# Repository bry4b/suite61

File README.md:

# suite61
 split ergo with numrow, arrows, and a stick

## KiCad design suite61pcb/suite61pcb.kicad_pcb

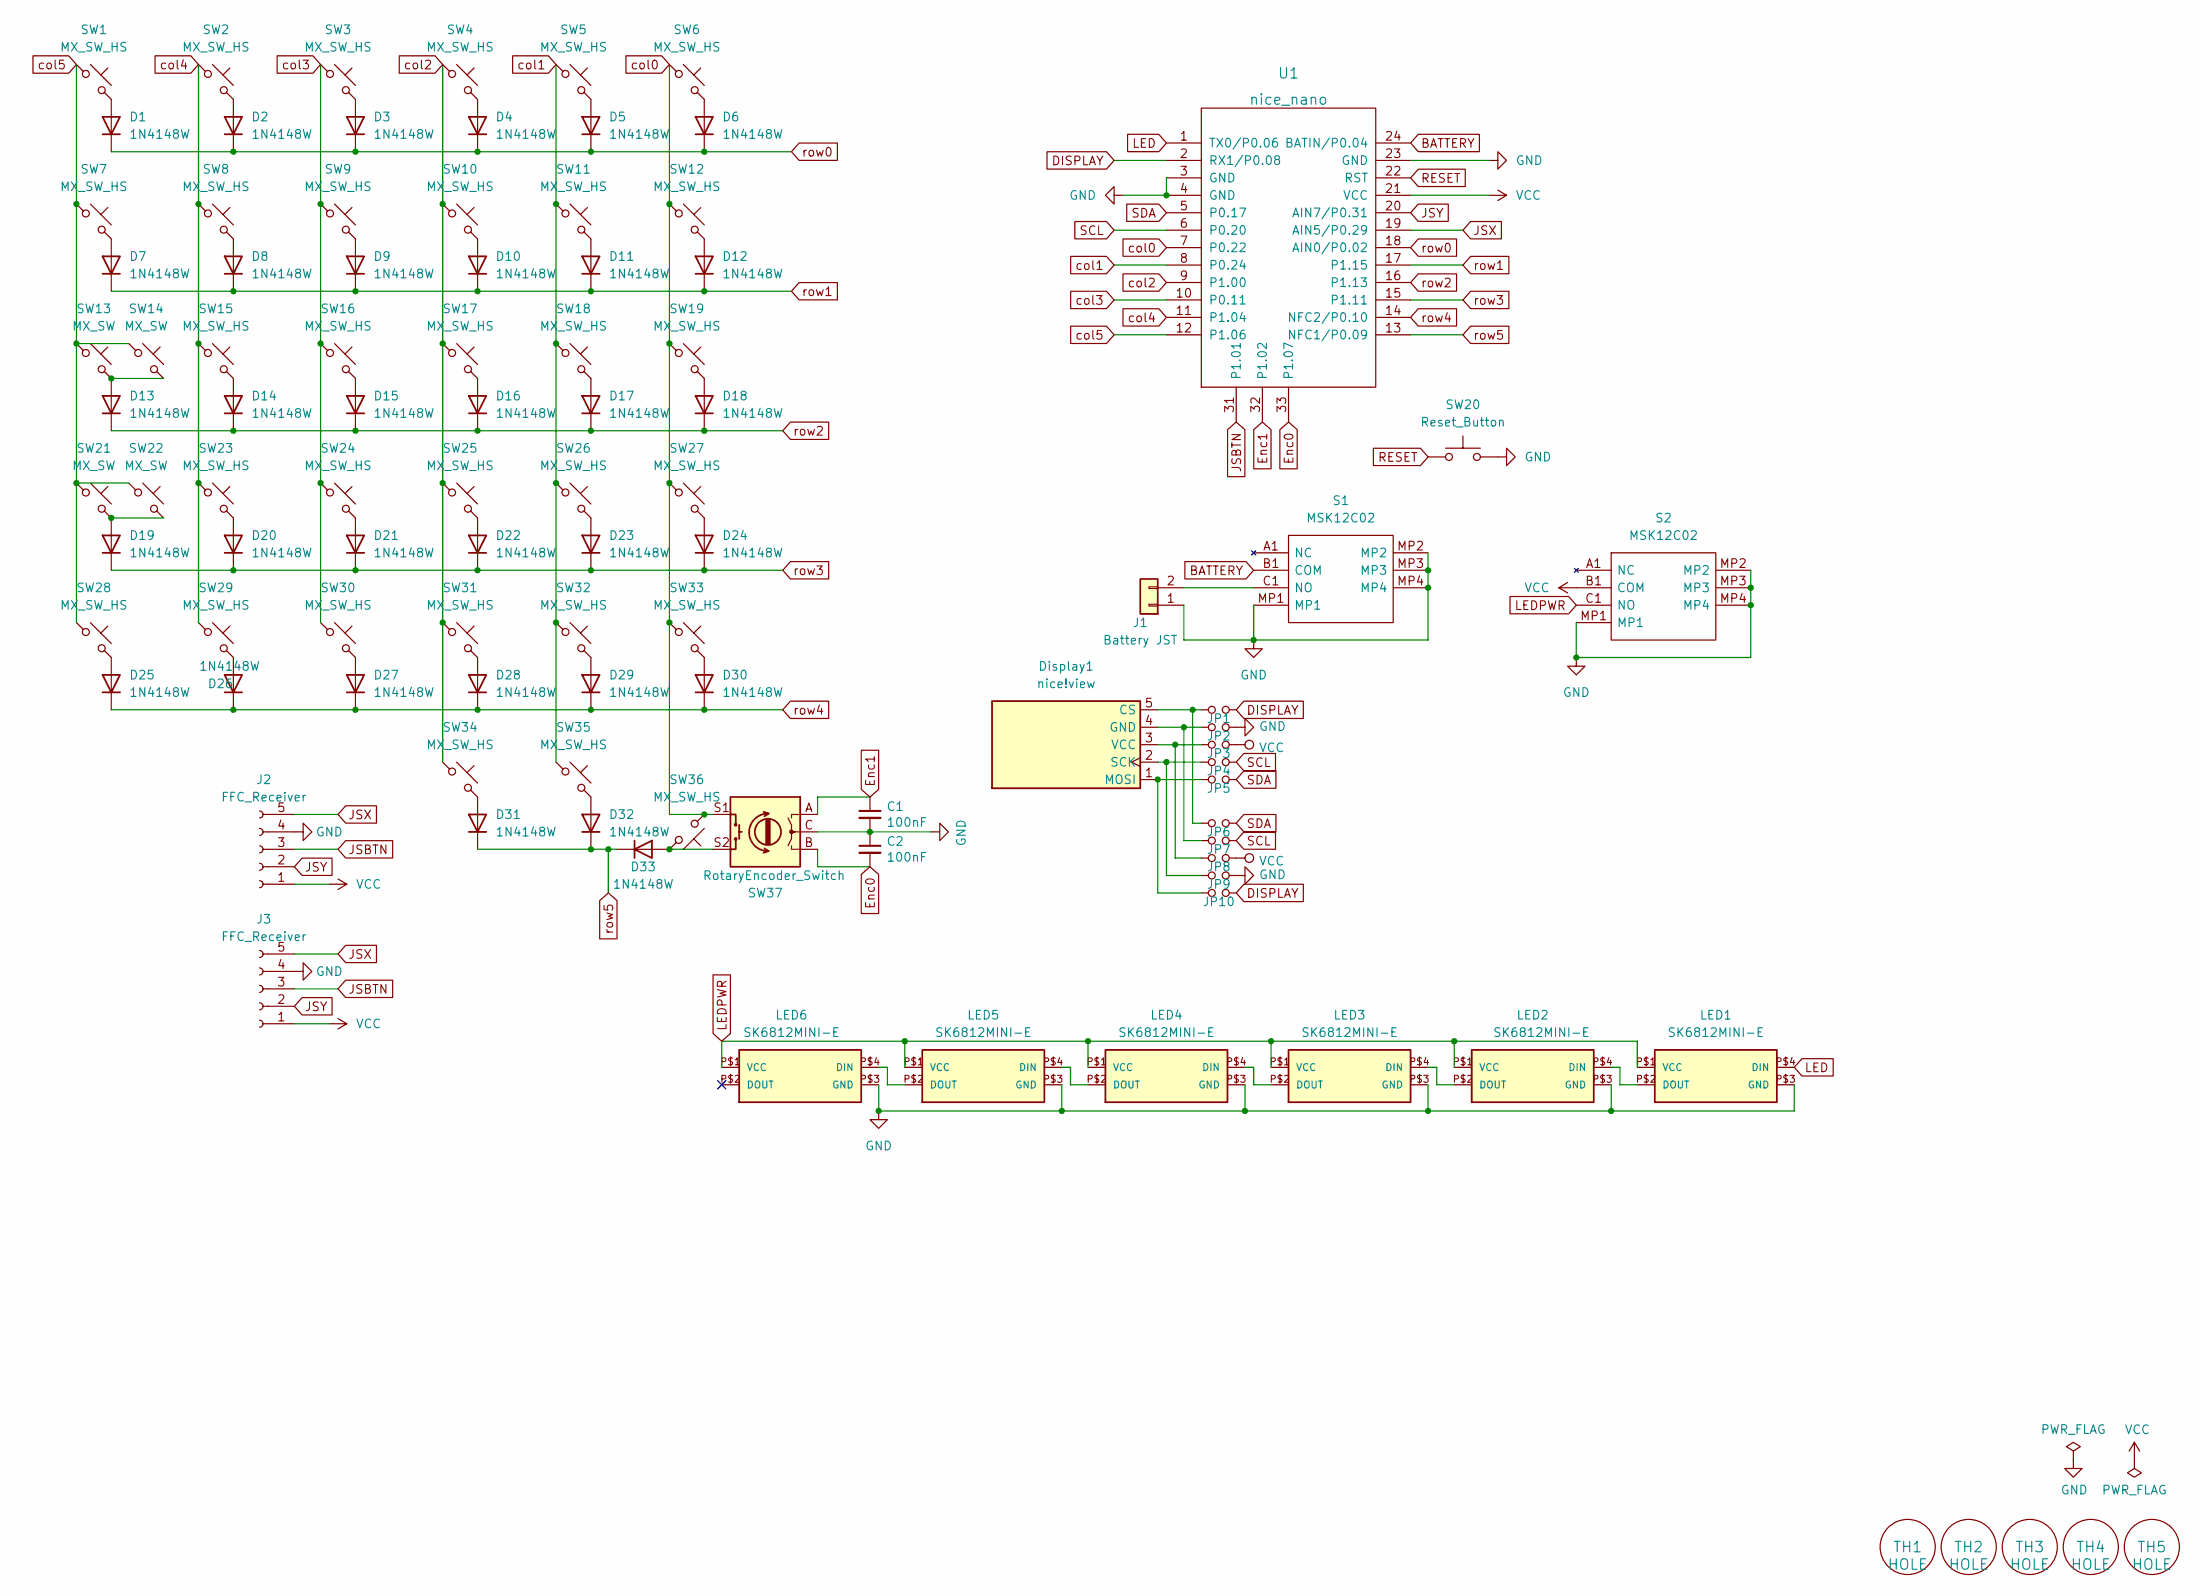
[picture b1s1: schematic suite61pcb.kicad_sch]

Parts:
C1, C2: 100nF; C_0805_2012Metric
D1, D2, D3, D4, D5, D6, D7, D8, D9, D10, D11, D12, D13, D14, D15, D16, D17, D18, D19, D20, D21, D22, D23, D24, D25, D26, D27, D28, D29, D30, D31, D32, D33: 1N4148W; D_SOD-123
Display1: nice!view; nice_view
J1: Battery JST; JST_SH_SM02B-SRSS-TB_1x02-1MP_P1.00mm_Horizontal
J2, J3: FFC_Receiver; 5034800500
JP1, JP2, JP3, JP4, JP5, JP6, JP7, JP8, JP9, JP10: Jumper_NO_Small; jumper
LED1, LED2, LED3, LED4, LED5, LED6: SK6812MINI-E; LED_6028R
S1, S2: MSK12C02; Manufacturer_Part_Number MSK12C02
SW1, SW2, SW3, SW4, SW5, SW6, SW8, SW9, SW10, SW11, SW12, SW15, SW16, SW17, SW18, SW19, SW23, SW24, SW25, SW26, SW27, SW29, SW30, SW31, SW32, SW33, SW34, SW36: MX_SW_HS; CherryMX_Hotswap
SW7, SW28, SW35: MX_SW_HS; CherryMX_Hotswap_1.5
SW13: MX_SW; SW_MX_HS_1.75u
SW14, SW21: MX_SW; STAB_MX_P__HS_2.25u
SW20: Reset_Button; SW_Push_1P1T_NO_CK_KMR2
SW22: MX_SW; CherryMX_Hotswap
SW37: RotaryEncoder_Switch; RotaryEncoder_EC11
TH1, TH2, TH3, TH4, TH5: HOLE; MountingHole_3.7mm
U1: nice_nano

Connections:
BATTERY: S1.B1 (COM), U1.24 (BATIN/P0.04)
DISPLAY: JP1.2, JP10.2, U1.2 (RX1/P0.08)
Enc0: C2.2, SW37.B, U1.33 (P1.07)
Enc1: C1.1, SW37.A, U1.32 (P1.02)
GND: C1.2, C2.1, J1.1, J2.4, J3.4, JP2.2, JP9.2, LED1.P$3 (GND), LED2.P$3 (GND), LED3.P$3 (GND), LED4.P$3 (GND), LED5.P$3 (GND), LED6.P$3 (GND), S1.MP1, S1.MP2, S1.MP3, S1.MP4, S2.MP1, S2.MP2, S2.MP3, S2.MP4, SW20.2, SW37.C, U1.3 (GND), U1.4 (GND), U1.23 (GND)
JSBTN: J2.3, J3.3, U1.31 (P1.01)
JSX: J2.5, J3.5, U1.19 (AIN5/P0.29)
JSY: J2.2, J3.2, U1.20 (AIN7/P0.31)
LED: LED1.P$4 (DIN), U1.1 (TX0/P0.06)
LEDPWR: LED1.P$1 (VCC), LED2.P$1 (VCC), LED3.P$1 (VCC), LED4.P$1 (VCC), LED5.P$1 (VCC), LED6.P$1 (VCC), S2.C1 (NO)
unnamed: D1.2 (A), SW1.2
unnamed: D2.2 (A), SW2.2
unnamed: D3.2 (A), SW3.2
unnamed: D4.2 (A), SW4.2
unnamed: D5.2 (A), SW5.2
unnamed: D6.2 (A), SW6.2
unnamed: D7.2 (A), SW7.2
unnamed: D8.2 (A), SW8.2
unnamed: D9.2 (A), SW9.2
unnamed: D10.2 (A), SW10.2
unnamed: D11.2 (A), SW11.2
unnamed: D12.2 (A), SW12.2
unnamed: D13.2 (A), SW13.2, SW14.2
unnamed: D14.2 (A), SW15.2
unnamed: D15.2 (A), SW16.2
unnamed: D16.2 (A), SW17.2
unnamed: D17.2 (A), SW18.2
unnamed: D18.2 (A), SW19.2
unnamed: D19.2 (A), SW21.2, SW22.2
unnamed: D20.2 (A), SW23.2
unnamed: D21.2 (A), SW24.2
unnamed: D22.2 (A), SW25.2
unnamed: D23.2 (A), SW26.2
unnamed: D24.2 (A), SW27.2
unnamed: D25.2 (A), SW28.2
unnamed: D26.2 (A), SW29.2
unnamed: D27.2 (A), SW30.2
unnamed: D28.2 (A), SW31.2
unnamed: D29.2 (A), SW32.2
unnamed: D30.2 (A), SW33.2
unnamed: D31.2 (A), SW34.2
unnamed: D32.2 (A), SW35.2
unnamed: D33.2 (A), SW36.1, SW37.S2
unnamed: Display1.1 (MOSI), JP5.1, JP10.1
unnamed: Display1.2 (SCK), JP4.1, JP9.1
unnamed: Display1.3 (VCC), JP3.1, JP8.1
unnamed: Display1.4 (GND), JP2.1, JP7.1
unnamed: Display1.5 (CS), JP1.1, JP6.1
unnamed: J1.2, S1.C1 (NO)
unnamed: LED1.P$2 (DOUT), LED2.P$4 (DIN)
unnamed: LED2.P$2 (DOUT), LED3.P$4 (DIN)
unnamed: LED3.P$2 (DOUT), LED4.P$4 (DIN)
unnamed: LED4.P$2 (DOUT), LED5.P$4 (DIN)
unnamed: LED5.P$2 (DOUT), LED6.P$4 (DIN)
RESET: SW20.1, U1.22 (RST)
SCL: JP4.2, JP7.2, U1.6 (P0.20)
SDA: JP5.2, JP6.2, U1.5 (P0.17)
VCC: J2.1, J3.1, JP3.2, JP8.2, S2.B1 (COM), U1.21 (VCC)
col0: SW6.1, SW12.1, SW19.1, SW27.1, SW33.1, SW36.2, SW37.S1, U1.7 (P0.22)
col1: SW5.1, SW11.1, SW18.1, SW26.1, SW32.1, SW35.1, U1.8 (P0.24)
col2: SW4.1, SW10.1, SW17.1, SW25.1, SW31.1, SW34.1, U1.9 (P1.00)
col3: SW3.1, SW9.1, SW16.1, SW24.1, SW30.1, U1.10 (P0.11)
col4: SW2.1, SW8.1, SW15.1, SW23.1, SW29.1, U1.11 (P1.04)
col5: SW1.1, SW7.1, SW13.1, SW14.1, SW21.1, SW22.1, SW28.1, U1.12 (P1.06)
row0: D1.1 (K), D2.1 (K), D3.1 (K), D4.1 (K), D5.1 (K), D6.1 (K), U1.18 (AIN0/P0.02)
row1: D7.1 (K), D8.1 (K), D9.1 (K), D10.1 (K), D11.1 (K), D12.1 (K), U1.17 (P1.15)
row2: D13.1 (K), D14.1 (K), D15.1 (K), D16.1 (K), D17.1 (K), D18.1 (K), U1.16 (P1.13)
row3: D19.1 (K), D20.1 (K), D21.1 (K), D22.1 (K), D23.1 (K), D24.1 (K), U1.15 (P1.11)
row4: D25.1 (K), D26.1 (K), D27.1 (K), D28.1 (K), D29.1 (K), D30.1 (K), U1.14 (NFC2/P0.10)
row5: D31.1 (K), D32.1 (K), D33.1 (K), U1.13 (NFC1/P0.09)

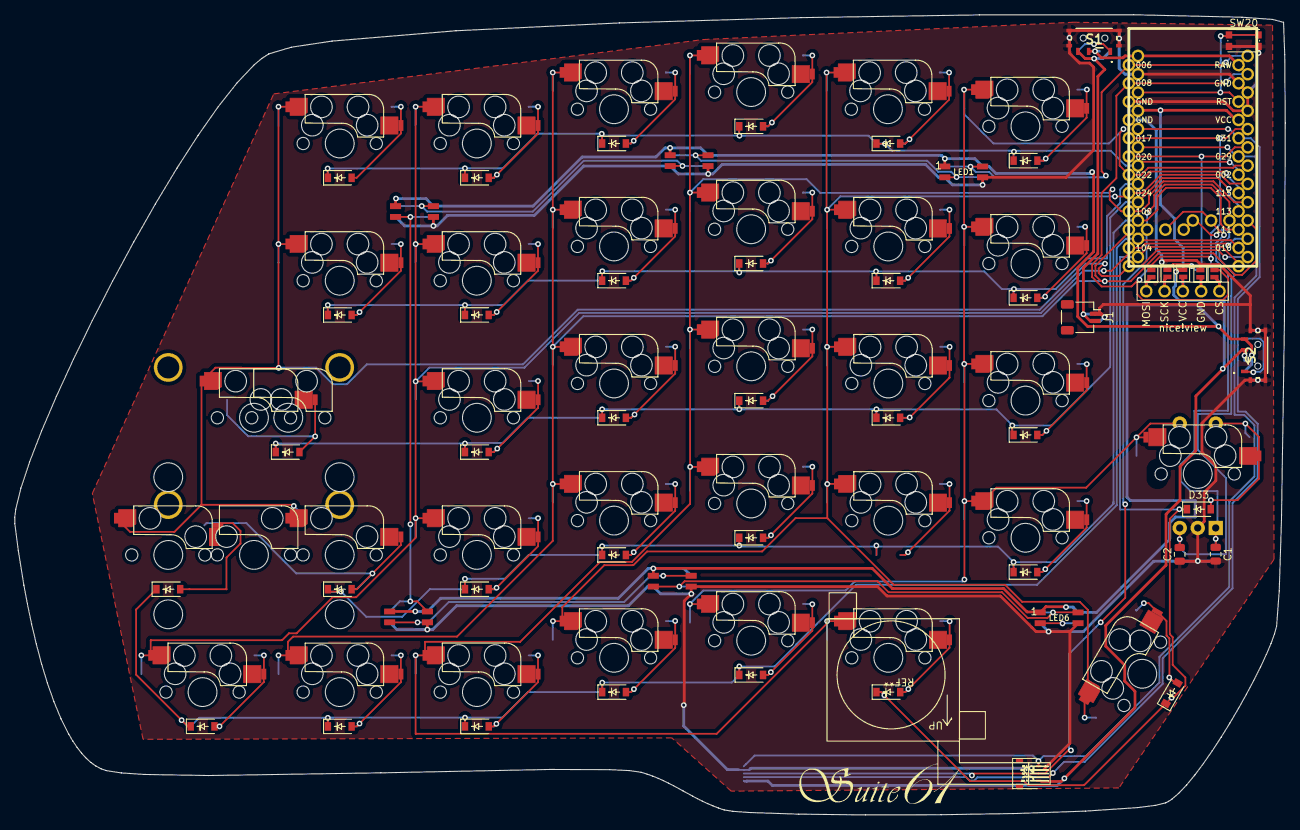
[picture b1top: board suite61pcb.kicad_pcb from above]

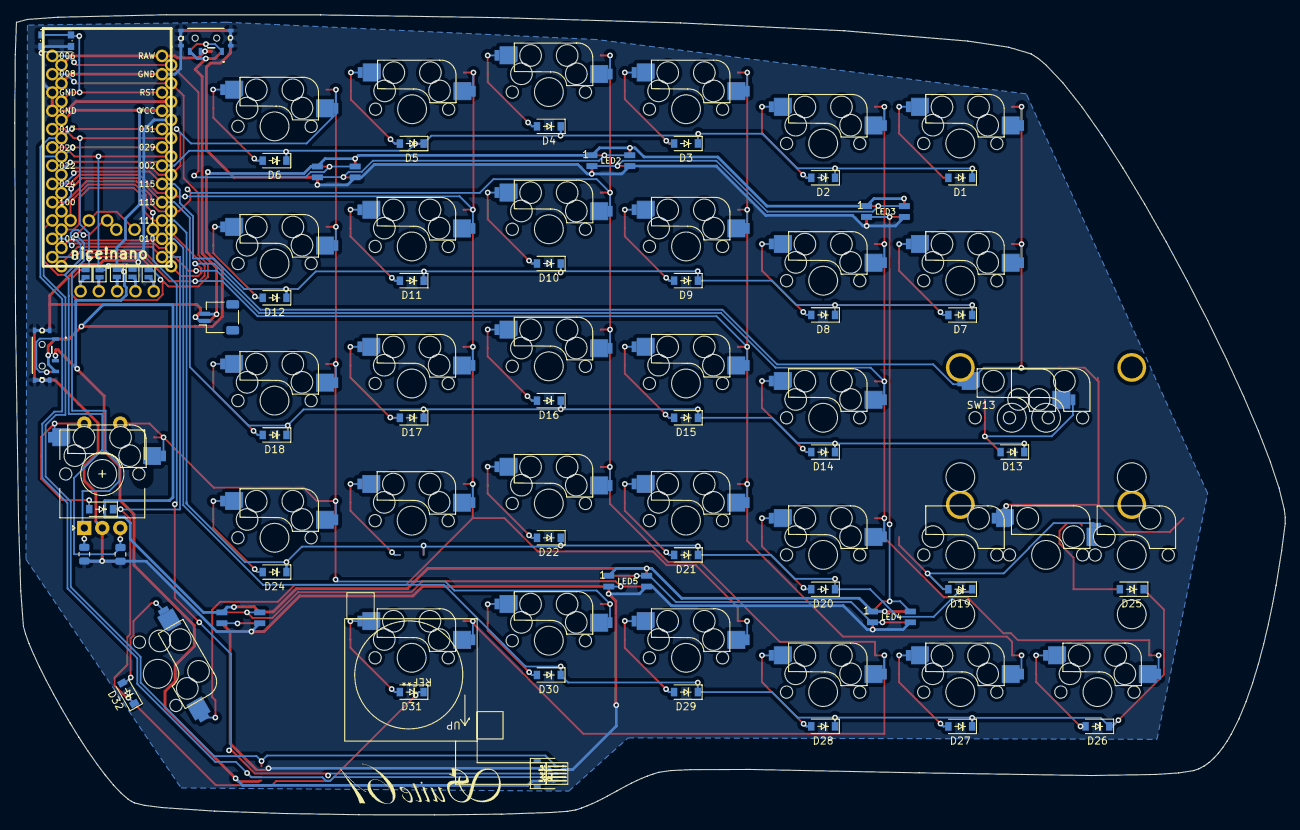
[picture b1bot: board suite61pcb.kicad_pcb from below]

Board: 2 copper layers, 176.5 x 111.1 mm, 99 parts (46 on the bottom side), 69 nets.

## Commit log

2023-02-20 create project
2023-02-20 Add submodules
2023-02-20 add footprint libraries
2023-02-20 update schematic
2023-02-20 create left pcb schematic
2023-02-20 Update matrix to 6x6
2023-02-20 create led underglow schematic, upload shield matrix KLE json
2023-02-21 update pcb
2023-02-22 update pcb and add keebio submod
2023-02-22 create suite61rev1
    changed joystick placement to be closer to spacebar for possible right half joystick support
2023-02-22 update pcb and schematic
2023-02-23 create edge outline
2023-02-25 update pcb
    check if oled header is right
2023-02-26 update pcb
    finished routing switch matrix, only need to do joystick & LEDs
    figure out how battery is gonna fit to keep underglow unobstructed
    decide on magnetic connector
2023-02-27 finished routing pcb, look into possible trrs + magnetic connection between halves
2023-02-28 routing & edge design
    finished routing pcb, added LED off switch
    drew edge design in illustrator subject to change
2023-03-08 create pcb edge cut
2023-03-22 update pcb w logo
2023-05-19 create gerbers
    pcb in production from jlcpcb!!!
